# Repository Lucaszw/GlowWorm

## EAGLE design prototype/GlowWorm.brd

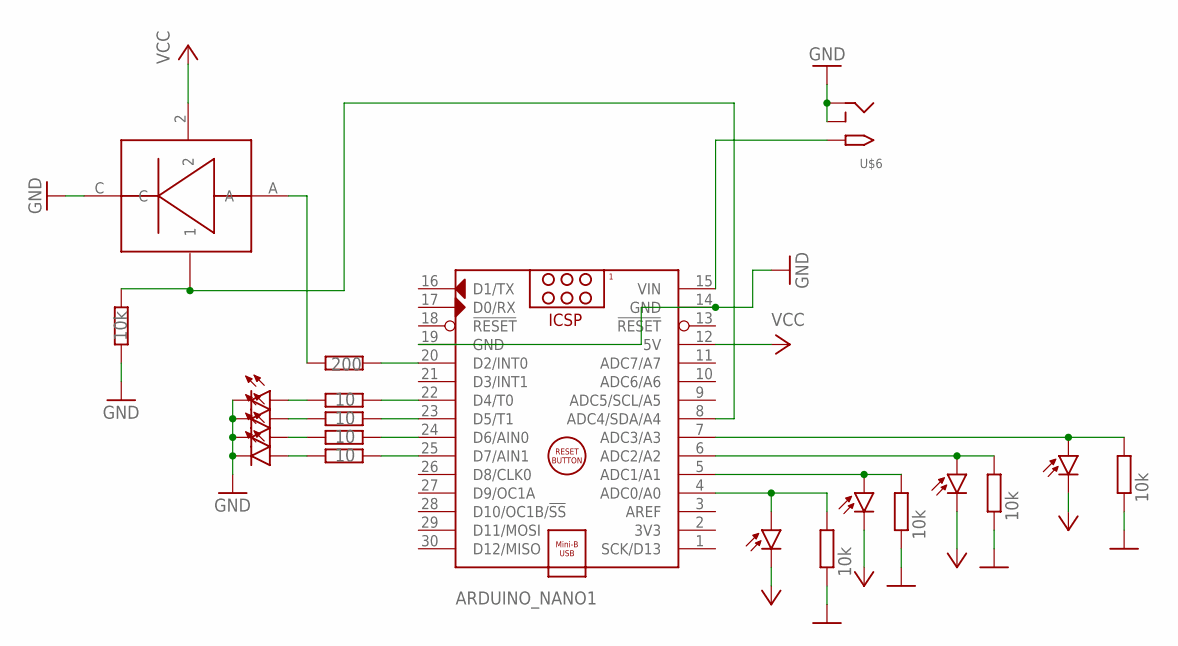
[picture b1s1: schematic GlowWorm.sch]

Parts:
ARDUINO_NANO1: ARDUINO_NANO
R1, R12, R13, R14: 10; 0207/7
R2, R5, R6, R7, R15: 10k; 0207/7
R11: 200; 0207/7
U$1, U$2, U$3, U$4: IR_RECEIVER; LED_RECEIVER5MM_H6,0MM
U$5, U$10, U$11, U$12: IR_TRANSMITTER; LED5MM_H6,0MM
U$6: 2.1MMJACKTHM; PJ-102A
U$9: ARCADE_LED_BTN

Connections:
GND: ARDUINO_NANO1.14 (GND), ARDUINO_NANO1.19 (GND), R2.1, R5.1, R6.1, R7.1, R15.1, U$5.K (C), U$6.RING, U$6.RING_SW, U$9.C, U$10.K (C), U$11.K (C), U$12.K (C)
unnamed: ARDUINO_NANO1.4 (ADC0/A0), R2.2, U$1.A (ANODE)
unnamed: ARDUINO_NANO1.5 (ADC1/A1), R6.2, U$3.A (ANODE)
unnamed: ARDUINO_NANO1.6 (ADC2/A2), R5.2, U$2.A (ANODE)
unnamed: ARDUINO_NANO1.7 (ADC3/A3), R7.2, U$4.A (ANODE)
unnamed: ARDUINO_NANO1.20 (D2/INT0), R11.2
unnamed: ARDUINO_NANO1.22 (D4/T0), R1.2
unnamed: ARDUINO_NANO1.23 (D5/T1), R12.2
unnamed: ARDUINO_NANO1.24 (D6/AIN0), R13.2
unnamed: ARDUINO_NANO1.25 (D7/AIN1), R14.2
unnamed: R1.1, U$5.A
unnamed: R12.1, U$10.A
unnamed: R13.1, U$11.A
unnamed: R14.1, U$12.A
unnamed: R11.1, U$9.A
unnamed: ARDUINO_NANO1.8 (ADC4/SDA/A4), R15.2, U$9.1
unnamed: ARDUINO_NANO1.15 (VIN), U$6.TIP
VCC: ARDUINO_NANO1.12 (5V), U$1.K (CATHODE), U$2.K (CATHODE), U$3.K (CATHODE), U$4.K (CATHODE), U$9.2

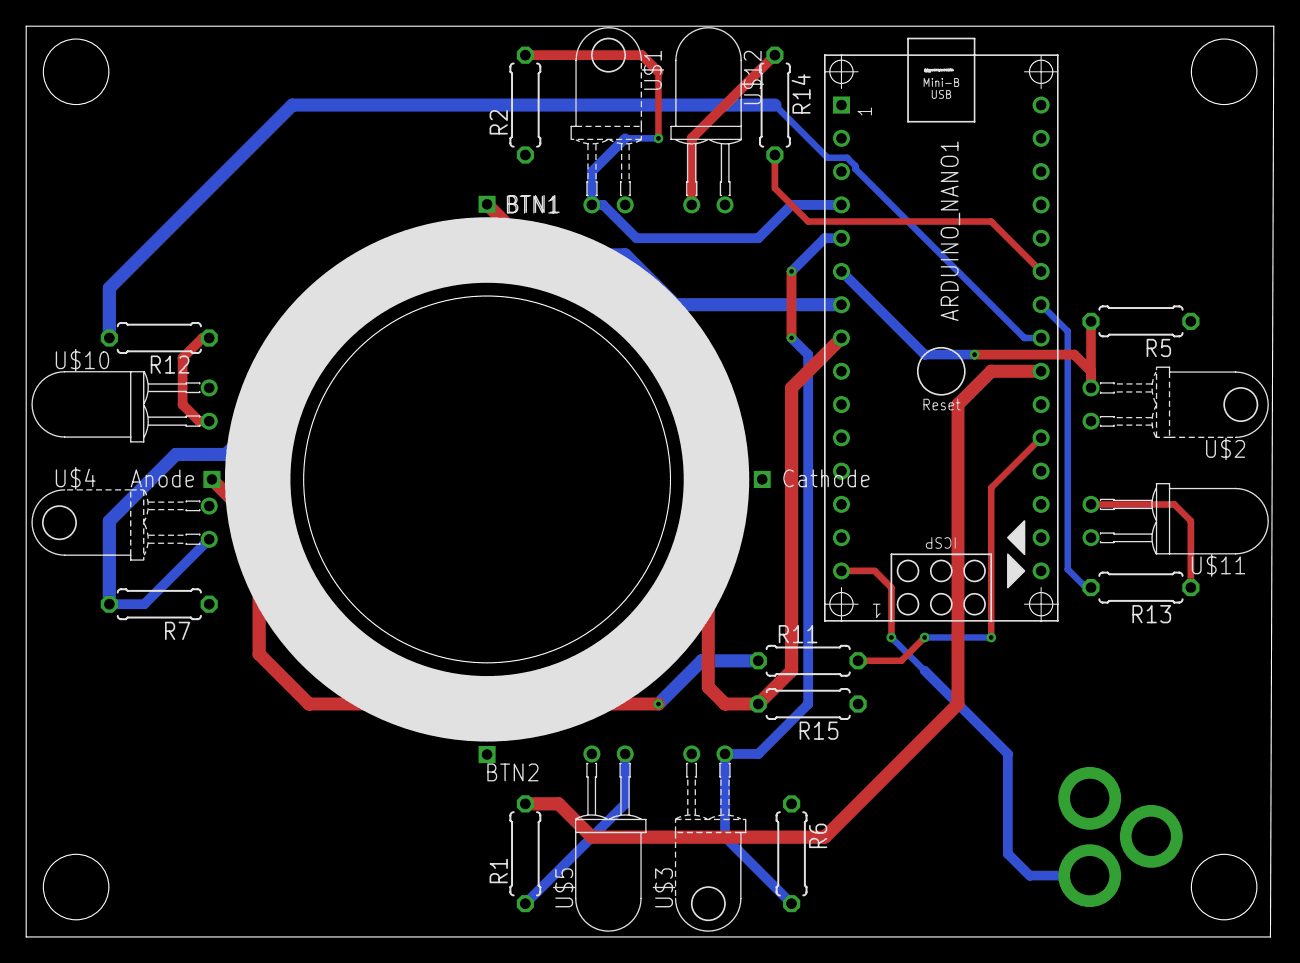
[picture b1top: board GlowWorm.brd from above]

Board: 2 copper layers, 95.2 x 69.5 mm, 21 parts (1 on the bottom side), 18 nets.

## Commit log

2020-07-16 add spining glow worms with video in background
2020-10-14 move all of the first playtest files into their own folder
2020-10-14 add prototype files
2020-10-14 add arduino code
